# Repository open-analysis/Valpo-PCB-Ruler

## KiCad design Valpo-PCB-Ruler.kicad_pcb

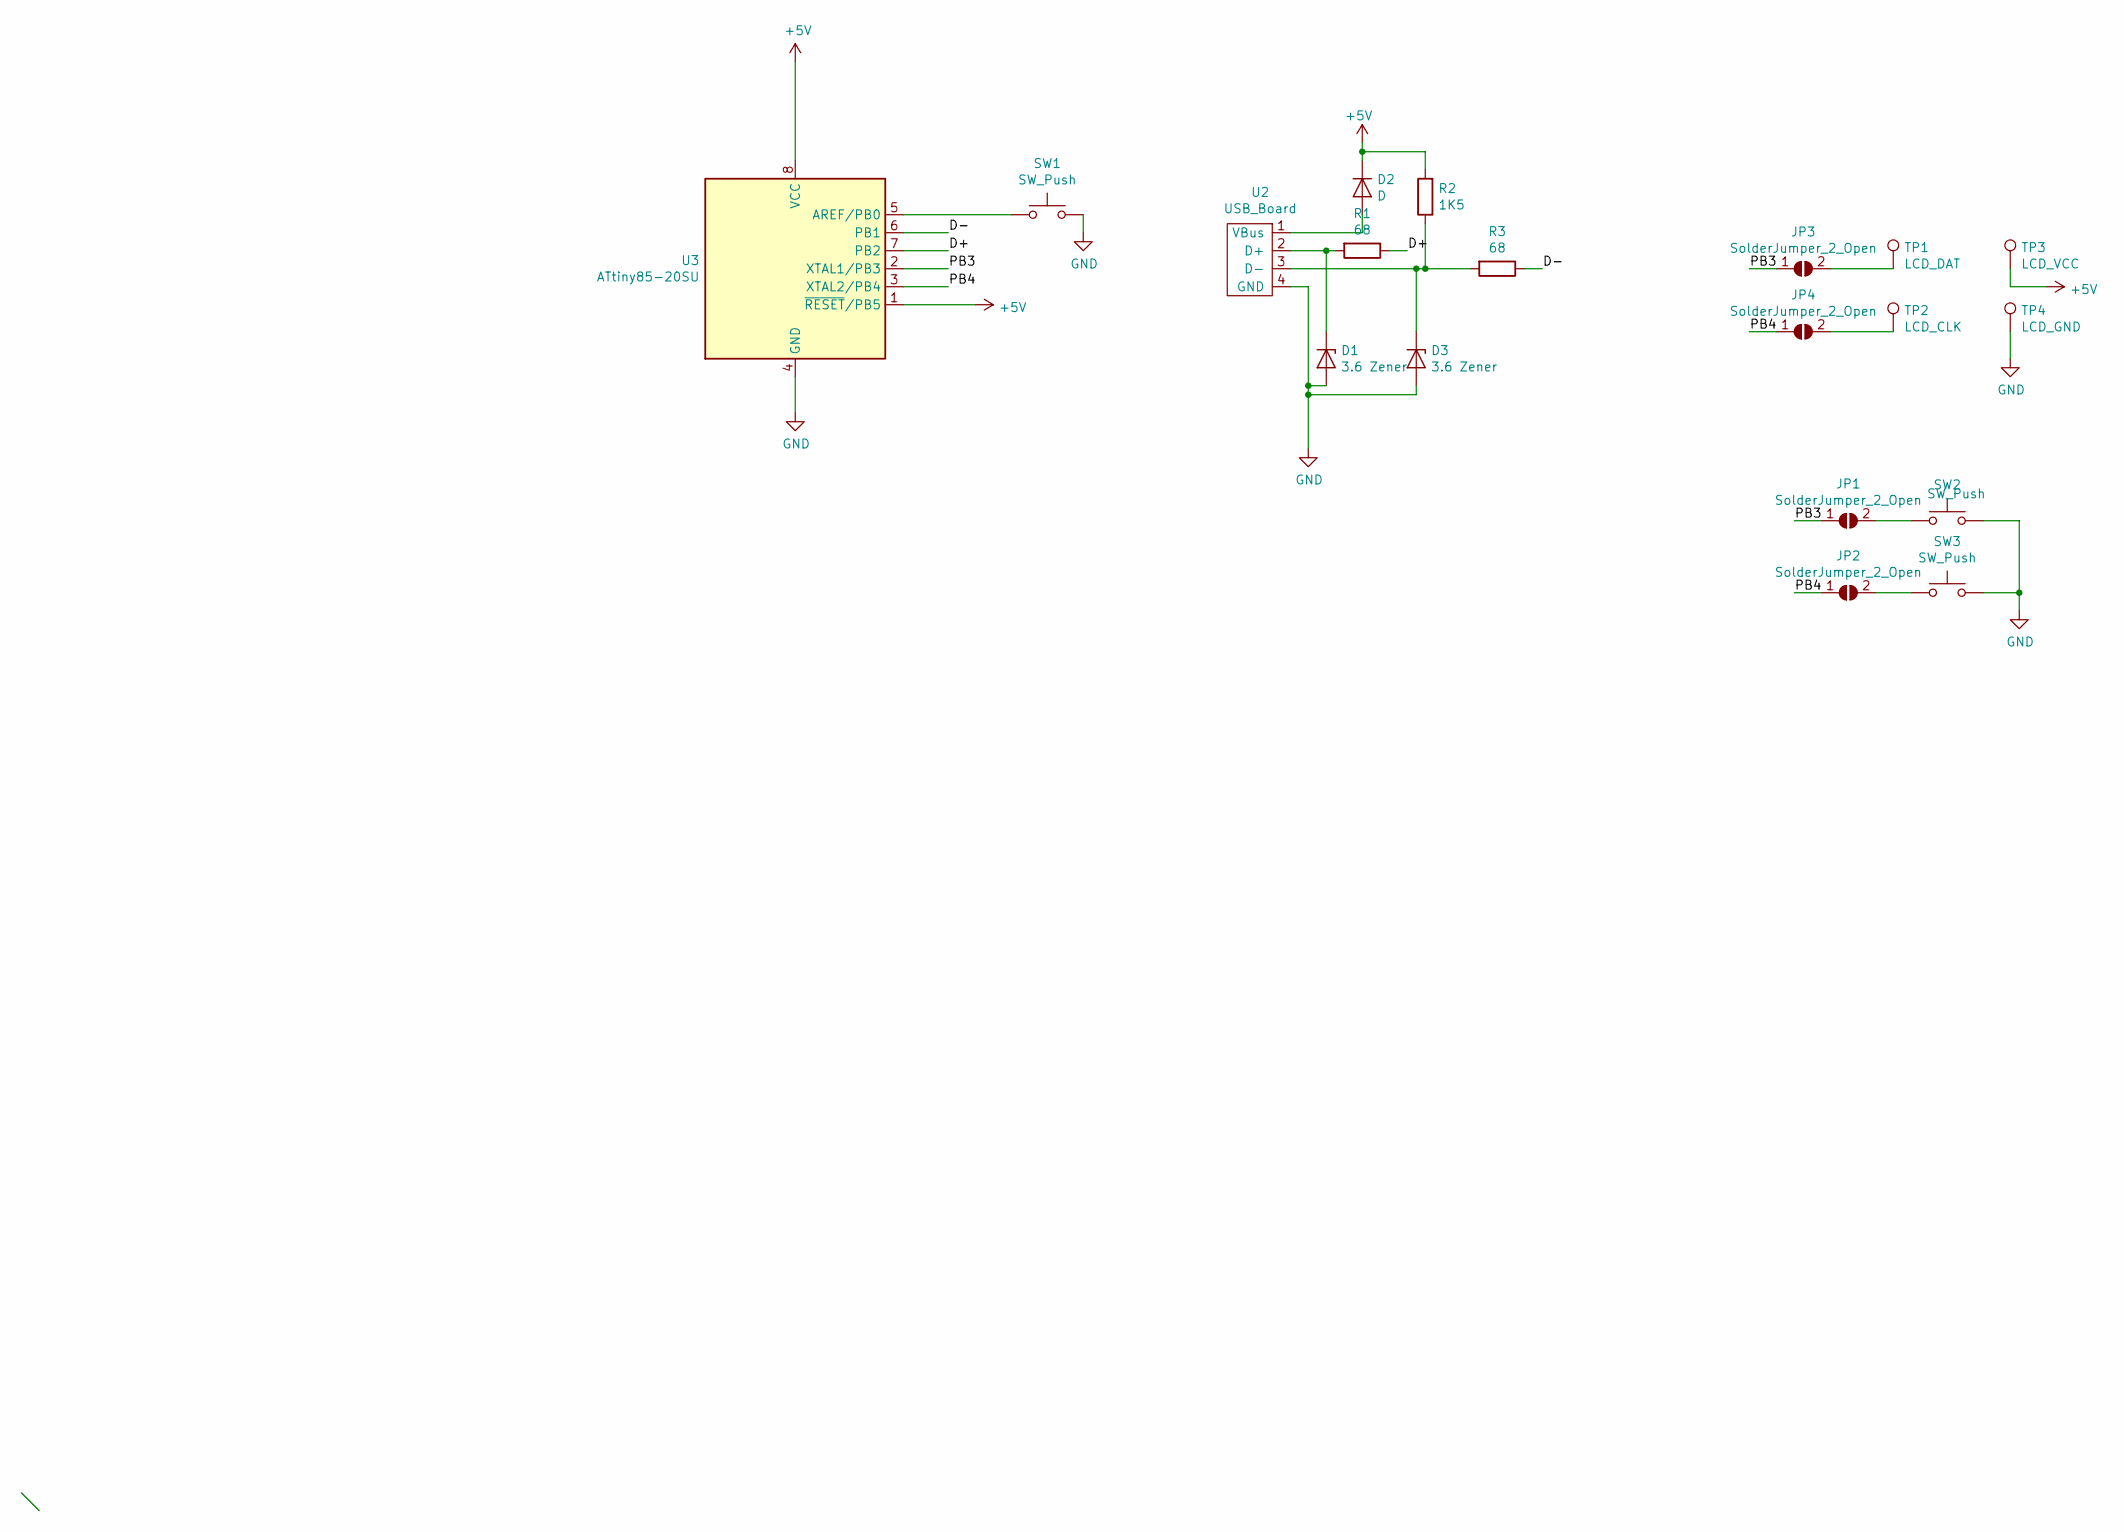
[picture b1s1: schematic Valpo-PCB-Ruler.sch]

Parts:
D1, D3: 3.6 Zener; D_0402_1005Metric
D2: D; D_0402_1005Metric
JP1, JP2, JP3, JP4: SolderJumper_2_Open; SolderJumper-2_P1.3mm_Open_Pad1.0x1.5mm
R1, R3: 68; R_0402_1005Metric
R2: 1K5; R_0402_1005Metric
SW1, SW2, SW3: SW_Push; SW_Push_SPST_NO_Alps_SKRK
TP1: LCD_DAT; TestPoint_Pad_D1.0mm
TP2: LCD_CLK; TestPoint_Pad_D1.0mm
TP3: LCD_VCC; TestPoint_Pad_D1.0mm
TP4: LCD_GND; TestPoint_Pad_1.0x1.0mm
U2: USB_Board
U3: ATtiny85-20SU; SOIJ-8_5.3x5.3mm_P1.27mm

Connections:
+5V: D2.1 (K), R2.2, TP3.1, U3.1 (~RESET~/PB5), U3.8 (VCC)
/D+: R1.1, U3.7 (PB2)
/D-: R3.1, U3.6 (PB1)
/PB3: JP1.1 (A), JP3.1 (A), U3.2 (XTAL1/PB3)
/PB4: JP2.1 (A), JP4.1 (A), U3.3 (XTAL2/PB4)
GND: D1.2 (A), D3.2 (A), SW1.2, SW2.2, SW3.2, TP4.1, U2.4 (GND), U3.4 (GND)
unnamed: D1.1 (K), R1.2, U2.2 (D+)
unnamed: D2.2 (A), U2.1 (VBus)
unnamed: D3.1 (K), R2.1, R3.2, U2.3 (D-)
unnamed: JP1.2 (B), SW2.1
unnamed: JP2.2 (B), SW3.1
unnamed: JP3.2 (B), TP1.1
unnamed: JP4.2 (B), TP2.1
unnamed: SW1.1, U3.5 (AREF/PB0)

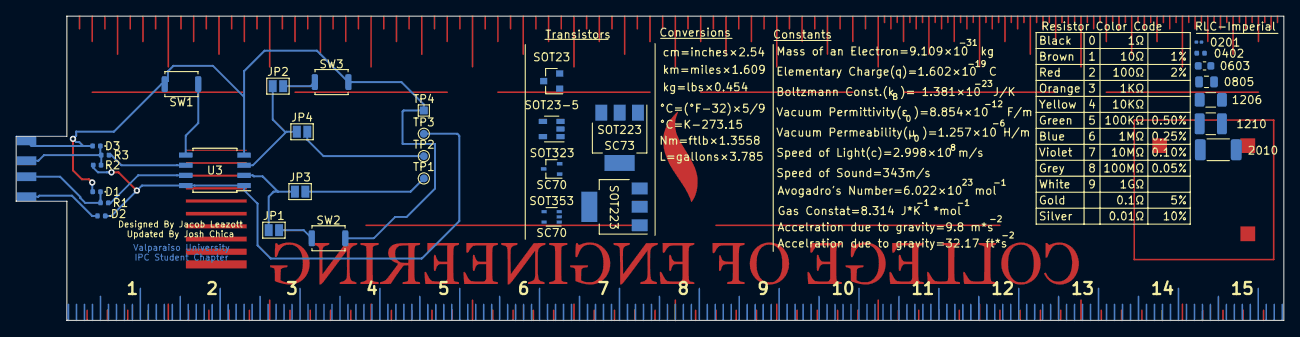
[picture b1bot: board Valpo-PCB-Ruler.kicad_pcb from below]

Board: 2 copper layers, 158.8 x 38.1 mm, 32 parts (32 on the bottom side), 14 nets.

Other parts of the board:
0201: R_0201_0603Metric
0402: R_0402_1005Metric
0603: R_0603_1608Metric
0805: R_0805_2012Metric
1206: R_1206_3216Metric
1210: R_1210_3225Metric
2010: R_2010_5025Metric
SOT23: SOT-23
SOT23-5: SOT-23-5
SOT223, SOT223#2: SOT-223
SOT323: SOT-323_SC-70
SOT353: SOT-353_SC-70-5

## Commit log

2021-08-11 Update basic design
    Reduced size of ruler from 8in to 6in. Adjusted positioning of front masks and screens to match new size. Removed most of the references on the back to make room for the new circuitry to be included.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
2021-08-12 Layout Set
    Set out layout and schematics for both LCD and push-buttons. Users will have the option to use either or depending on which solder bridges they connect. Board USB also added to the device, may need t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
2021-08-16 Reverse USB side
    Moved the USB to be on the other side of the board to maintain the sanctity of the zero on the left side (for the imperial units).
    Reduced transistor diagrams to not some of the smaller diagrams. Added additional hardware to allow the ATtiny to work with USB.
    Added some Mechanical engineering focused constants (Avogadro's Number, Gas Constant, Accl due to gravity in metric & imperial)
2021-08-16 Reduce USB size
    Brought the sides of the USB down to more closely fit the width of the pads.
2021-08-16 Regenerated Gerber files
2021-08-16 Remove original zip file
